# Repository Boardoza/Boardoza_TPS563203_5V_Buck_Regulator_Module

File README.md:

# Boardoza TPS563203 5V Regulator Module

The **Boardoza TPS563203 5V Regulator Module** is a compact and efficient DC-DC buck (step-down) converter designed to provide a stable **5V output** from a wide **7V–17V DC input** range. It is based on the **Texas Instruments TPS563203** synchronous buck regulator, known for its high efficiency and low quiescent current.

This module is ideal for powering **microcontrollers, sensors, communication modules, and embedded systems** that require a reliable 5V supply from higher-voltage sources such as adapters, batteries, or industrial power rails. Its small form factor and robust thermal performance make it suitable for both prototyping and production use.

## [Click here to purchase!](https://www.ozdisan.com/ureticiler/boardoza)

| Front Side | Back Side |
|:---:|:---:|
|  |  |

---

## Key Features

- **Wide Input Voltage Range:** Supports 7V to 17V DC input for flexible power sources.  
- **Stable 5V Output:** Provides a fixed and regulated 5V DC output suitable for logic and embedded systems.  
- **High Output Current Capability:** Delivers up to 2A continuous output current.  
- **High Efficiency Buck Topology:** Synchronous step-down conversion for reduced power loss.  
- **Low Quiescent Current:** Optimized for power-efficient designs with minimal standby consumption.  
- **Integrated Soft-Start:** Ensures controlled startup to protect connected loads.

---

## Technical Specifications

**Model:** TPS563203 5V  
**Manufacturer:** Boardoza  
**Manufacturer IC:** Texas Instruments  
**Regulator Type:** DC-DC Buck (Step-Down) Converter  
**Input Voltage:** 7V – 17V DC  
**Output Voltage:** 5V DC  
**Output Current:** Up to 2A  
**Switching Frequency:** 600 kHz  
**Quiescent Current:** 110 µA (typ.)  
**Soft-Start Time:** 1.4 ms (fixed)  
**Reference Voltage Accuracy:** ±1.5% (25°C), ±2% (–40°C to +125°C)  
**Operating Temperature:** –40°C to +125°C  
**Board Dimensions:** 20 mm × 40 mm  

---

## Board Pinout

### **( J1 ) Input Connector**

| Pin Number | Pin Name | Description |
|:---:|:---:|---|
| 1 | VIN | DC Input Voltage (7V – 17V) |
| 2 | GND | Ground |

### **( J2 ) Output Connector**

| Pin Number | Pin Name | Description |
|:---:|:---:|---|
| 1 | VOUT | Regulated +5V Output |
| 2 | GND | Ground |

---

## Board Dimensions

---

## Step Files

[Boardoza TPS563203 5V.step](./assets/TPS563203-5V%20Step.step)

---

## Datasheet

[TPS563203 5V Datasheet.pdf](./assets/TPS563203-5V%20Datasheet.pdf)

---

## Version History

- **V1.0.0** – Initial Release

---

## Support

- If you have any questions or need support, please contact **support@boardoza.com**

---

## **License**
### **Hardware Design**

[![CC BY-SA 4.0][cc-by-sa-shield]][cc-by-sa]

All hardware design files are licensed under [Creative Commons Attribution-ShareAlike 4.0 International License][cc-by-sa].

[cc-by-sa]: http://creativecommons.org/licenses/by-sa/4.0/
[cc-by-sa-shield]: https://img.shields.io/badge/License-CC%20BY--SA%204.0-lightgrey.svg

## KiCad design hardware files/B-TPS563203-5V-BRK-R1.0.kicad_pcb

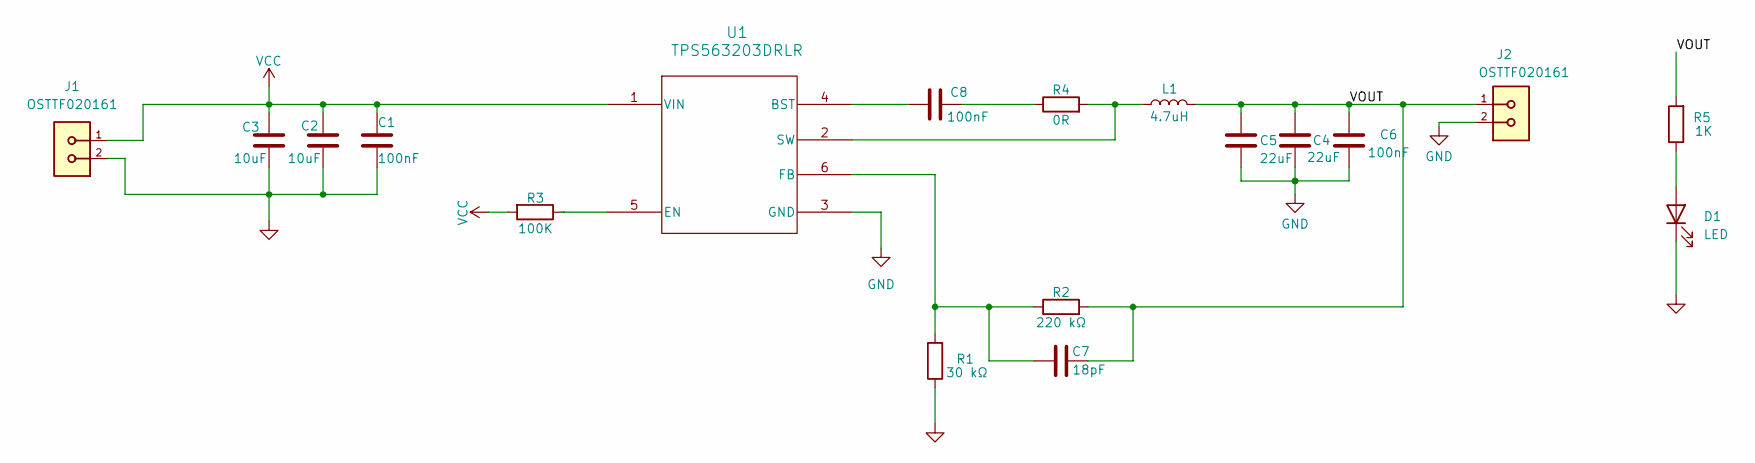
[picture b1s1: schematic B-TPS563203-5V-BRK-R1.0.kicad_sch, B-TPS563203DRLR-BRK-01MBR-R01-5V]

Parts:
C1, C6, C8: 100nF; C_0603_1608Metric; MPN CL10B104KB8NNNC
C2, C3: 10uF; C_0603_1608Metric; MPN MCF03MTX250106
C4, C5: 22uF; C_0603_1608Metric; MPN GRM188R61A226ME15D
C7: 18pF; C_0603_1608Metric; MPN MCF03JTN500180
D1: LED; LED_0603_1608Metric; MPN LTST-C190KRKT
J1, J2: OSTTF020161; OST_OSTTF020161; MPN DG350-3.5-02P-12-00AH
L1: 4.7uH; L_7.3x7.3_H4.5; MPN SRI0704-4R7M
R1: 30 kΩ; R_0603_1608Metric; MPN 0603SAJ0303T5E
R2: 220 kΩ; R_0603_1608Metric; MPN CRT03F7E2203
R3: 100K; R_0603_1608Metric; MPN CRT03F7E1003
R4: 0R; R_0603_1608Metric; MPN CRT03J7-R0R0
R5: 1K; R_0603_1608Metric; MPN RC0603JR-071KL
U1: TPS563203DRLR; SOT_07SDRLR_TEX; MPN TPS563203DRLR

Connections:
/VOUT: C4.1, C5.1, C6.1, C7.2, J2.1, L1.2, R2.2, R5.2
GND: C1.2, C2.2, C3.2, C4.2, C5.2, C6.2, D1.1 (K), J1.2, J2.2, R1.1, U1.3 (GND)
unnamed: C8.1, R4.1
unnamed: D1.2 (A), R5.1
unnamed: C8.2, U1.4 (BST)
unnamed: R3.1, U1.5 (EN)
unnamed: C7.1, R1.2, R2.1, U1.6 (FB)
unnamed: L1.1, R4.2, U1.2 (SW)
VCC: C1.1, C2.1, C3.1, J1.1, R3.2, U1.1 (VIN)

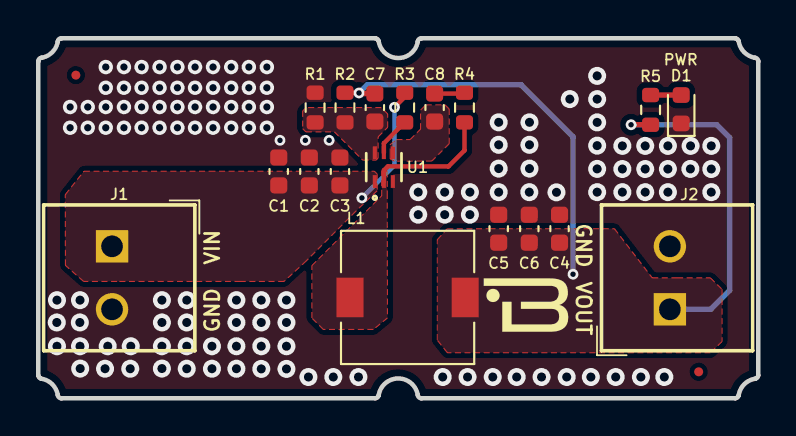
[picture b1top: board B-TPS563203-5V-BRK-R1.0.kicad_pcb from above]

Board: 2 copper layers, 40.0 x 20.0 mm, 18 parts (0 on the bottom side), 9 nets.
